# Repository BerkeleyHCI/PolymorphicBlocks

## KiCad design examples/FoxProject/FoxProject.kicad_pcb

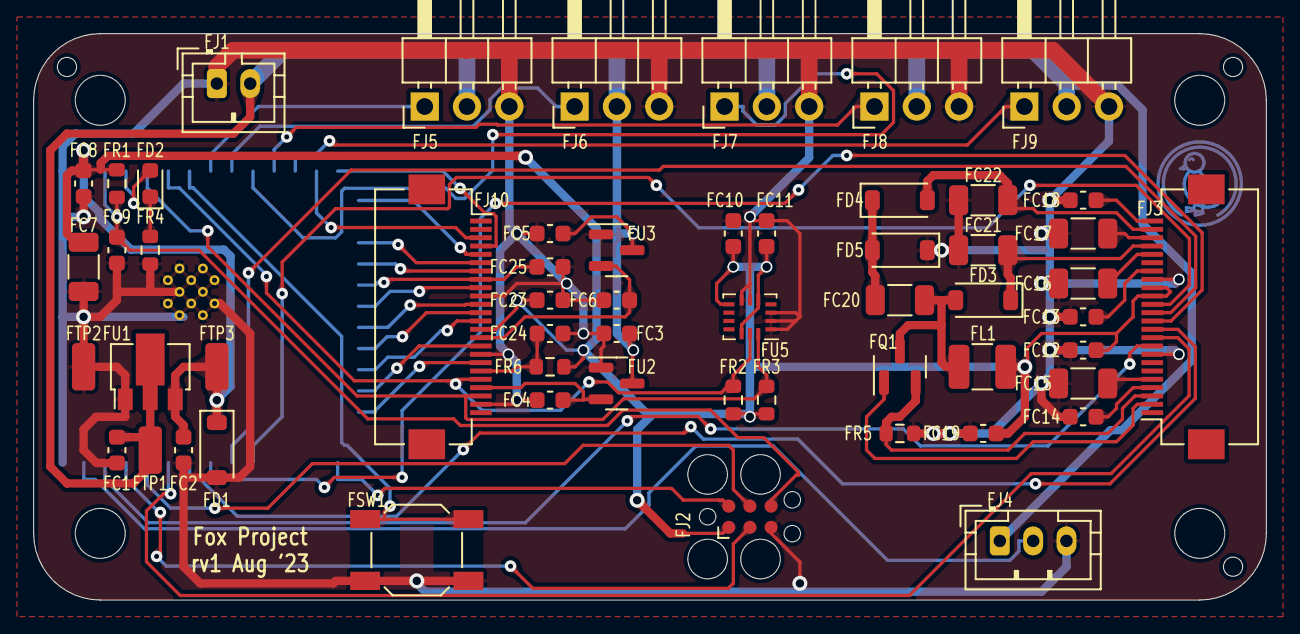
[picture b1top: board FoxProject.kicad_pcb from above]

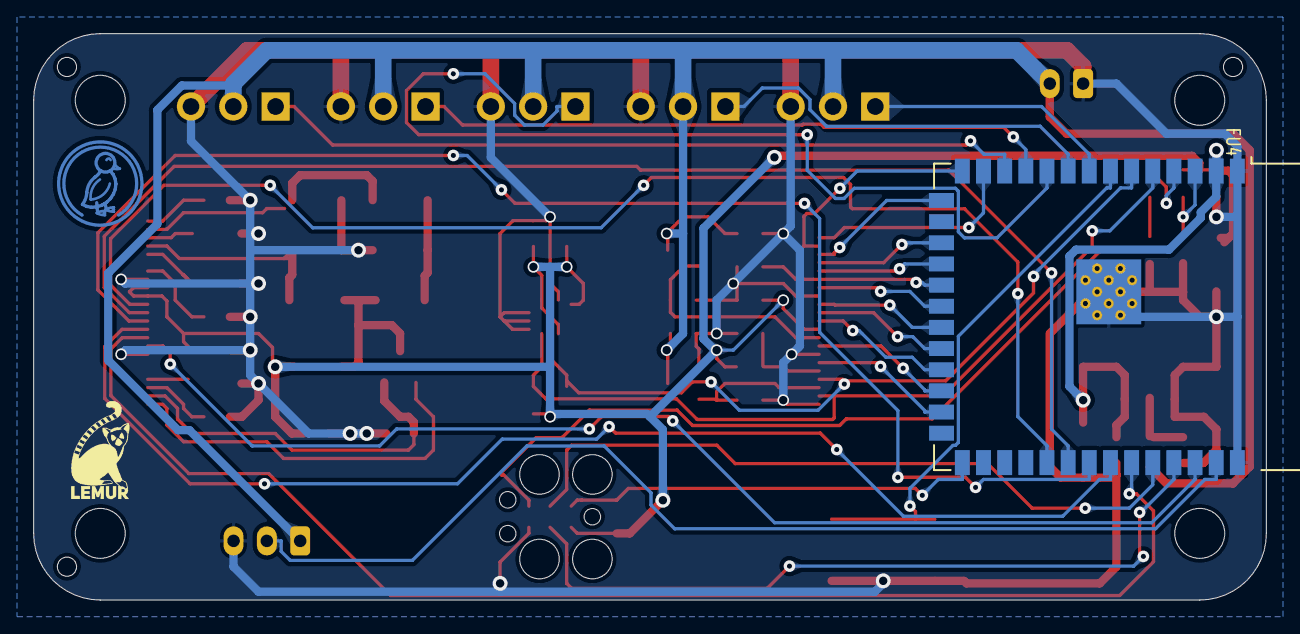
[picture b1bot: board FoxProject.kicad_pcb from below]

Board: 2 copper layers, 74.0 x 34.0 mm, 66 parts (3 on the bottom side), 51 nets.

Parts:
FC1, FC2, FC3, FC4, FC5, FC6, FC8, FC9, FC10, FC11, FC12, FC13, FC14, FC18, FC19, FC23, FC24, FC25: C_0603_1608Metric
FC7, FC15, FC16, FC17, FC20, FC21, FC22: C_1206_3216Metric
FD1: BZT52C3V6 (SMC(Sangdest Microelectronicstronic (N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; D_SOD-123
FD2: LED_0603_1608Metric
FD3, FD4, FD5: B5817W (Guangdong Hottech) - 20V 450mV@1A 300mA S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; D_SOD-123
FH1, FH2, FH3: JlcToolingHole_1.152mm
FJ1: B2B-PH-K (JST); JST_PH_B2B-PH-K_1x02_P2.00mm_Vertical
FJ2: Tag-Connect_TC2030-IDC-FP_2x03_P1.27mm_Vertical
FJ3, FJ10: AFC01-S24FCA-00 (Jushuo); Hirose_FH12-24S-0.5SH_1x24-1MP_P0.50mm_Horizontal
FJ4: B3B-PH-K (JST); JST_PH_B3B-PH-K_1x03_P2.00mm_Vertical
FJ5, FJ6, FJ7, FJ8, FJ9: PinHeader2.54 1x3 Horizontal (Generic); PinHeader_1x03_P2.54mm_Horizontal
FL1: L_1210_3225Metric
FQ1: AO3400A (Alpha & Omega Semicon) - 30V 5.7A 26.5m?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; SOT-23
FR1, FR2, FR3, FR4, FR5, FR6: R_0603_1608Metric
FSW1: 5.1mm switch; SW_SPST_SKQG_WithoutStem
FTP1: 5015 (Keystone) - pwr; TestPoint_TE_RCT_0805
FTP2: 5015 (Keystone) - gnd; TestPoint_TE_RCT_0805
FTP3: 5015 (Keystone) - v3v3; TestPoint_TE_RCT_0805
FU1: AP7215-33YG-13 (Diodes Incorporated); SOT-89-3
FU2: XC6206P252MR (Torex Semiconductor Ltd); SOT-23
FU3: XC6206P122MR-G (Torex Semiconductor Ltd); SOT-23
FU4: ESP32-S3-WROOM-1-N16R8 (Espressif Systems); ESP32-S3-WROOM-1
FU5: LSM6DS3TR-C (STMicroelectronics); Bosch_LGA-14_3x2.5mm_P0.5mm
H10, H11, H12, H13: MountingHole_3mm
UU4: Duck; Symbol_Duckling
UU5: Lemur; Symbol_LemurSmall

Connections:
Fcam.device.reset: FC24.1, FJ10.19, FR6.2
Fcam.dvp8.href: FJ10.16, FU4.24
Fcam.dvp8.pclk: FC25.1, FJ10.8, FU4.19
Fcam.dvp8.vsync: FJ10.18, FU4.25
Fcam.dvp8.xclk: FJ10.12, FU4.22
Fcam.dvp8.y0: FJ10.6, FU4.17
Fcam.dvp8.y1: FJ10.4, FU4.14
Fcam.dvp8.y2: FJ10.3, FU4.13
Fcam.dvp8.y3: FJ10.5, FU4.15
Fcam.dvp8.y4: FJ10.7, FU4.18
Fcam.dvp8.y5: FJ10.9, FU4.20
Fcam.dvp8.y6: FJ10.11, FU4.21
Fcam.dvp8.y7: FJ10.13, FU4.23
Fepd.boost.boot_cap.neg: FC20.2, FD4.1, FD5.2
Fepd.boost.inductor.b: FC20.1, FD3.2, FL1.2, FQ1.3
Fepd.boost.neg_out: FC22.2, FD4.2, FJ3.23
Fepd.boost.pos_out: FC21.1, FD3.1, FJ3.21
Fepd.busy: FJ3.9, FU4.38
Fepd.cs: FJ3.12, FU4.33
Fepd.dc: FJ3.11, FU4.34
Fepd.device.gdr: FJ3.2, FQ1.1
Fepd.device.rese: FJ3.3, FQ1.2, FR5.1
Fepd.device.vcom: FC18.1, FJ3.24
Fepd.device.vdd1v8: FC13.1, FJ3.18
Fepd.device.vgh: FC15.1, FJ3.5
Fepd.device.vgl: FC14.2, FJ3.4
Fepd.device.vsh: FC16.1, FJ3.20
Fepd.device.vsl: FC17.2, FJ3.22
Fepd.reset: FJ3.10, FU4.35
Fepd.spi.mosi: FJ3.14, FU4.31
Fepd.spi.sck: FJ3.13, FU4.32
Fgnd: FC1.2, FC2.2, FC3.2, FC4.2, FC5.2, FC6.2, FC7.2, FC8.2, FC9.2, FC10.2, FC11.2, FC12.2, FC13.2, FC14.1, FC15.2, FC16.2, FC17.1, FC18.2, FC19.2, FC21.2, FC22.1, FC23.2, FC24.2, FC25.2, FD1.2, FD5.1, FJ1.1, FJ2.5, FJ3.8, FJ3.17, FJ4.3, FJ5.3, FJ6.3, FJ7.3, FJ8.3, FJ9.3, FJ10.10, FJ10.17, FJ10.23, FR4.2, FR5.2, FSW1.2, FTP2.1, FU1.1, FU2.1, FU3.1, FU4.1, FU4.40, FU4.41, FU5.1, FU5.2, FU5.3, FU5.6, FU5.7
Fi2c_chain_0.scl: FJ10.20, FR2.2, FU4.6, FU5.13
Fi2c_chain_0.sda: FJ10.22, FR3.2, FU4.5, FU5.14
Fled.res.a: FD2.1, FR4.1
Fled.signal: FD2.2, FU4.4
Fmcu.program_boot_node: FJ2.2, FU4.27
Fmcu.program_en_node: FC9.1, FJ2.6, FR1.2, FU4.3
Fmcu.program_uart_node.a_tx: FJ2.3, FU4.37
Fmcu.program_uart_node.b_tx: FJ2.4, FU4.36
Fpixels.din: FJ4.2, FU4.39
Fpwr: FC1.1, FC3.1, FC5.1, FJ1.2, FJ4.1, FJ5.2, FJ6.2, FJ7.2, FJ8.2, FJ9.2, FTP1.1, FU1.2, FU2.3, FU3.3
Fservos[0].pwm: FJ5.1, FU4.8
Fservos[1].pwm: FJ6.1, FU4.9
Fservos[2].pwm: FJ7.1, FU4.10
Fservos[3].pwm: FJ8.1, FU4.11
Fservos[4].pwm: FJ9.1, FU4.12
Fsw.out: FSW1.1, FU4.7
Fv1v2: FC6.1, FJ10.15, FU3.2
Fv2v5: FC4.1, FJ10.21, FU2.2
Fv3v3: FC2.1, FC7.1, FC8.1, FC10.1, FC11.1, FC12.1, FC19.1, FC23.1, FD1.1, FJ2.1, FJ3.15, FJ3.16, FJ10.14, FL1.1, FR1.1, FR2.1, FR3.1, FR6.1, FTP3.1, FU1.3, FU4.2, FU5.5, FU5.8, FU5.12

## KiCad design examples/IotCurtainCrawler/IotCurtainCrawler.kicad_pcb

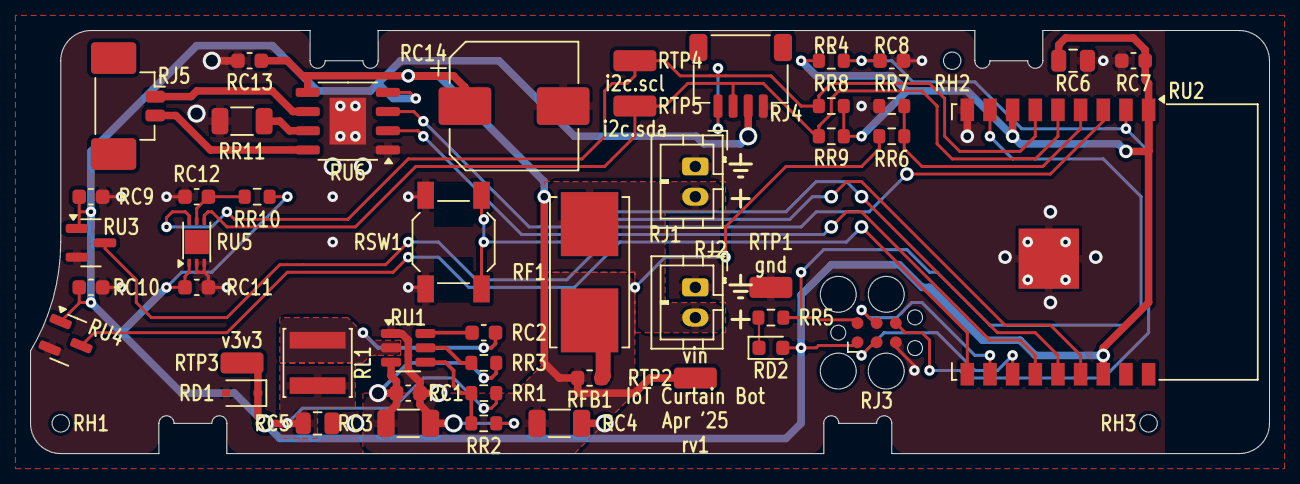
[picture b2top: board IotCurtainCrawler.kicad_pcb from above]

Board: 2 copper layers, 82.0 x 28.0 mm, 50 parts (0 on the bottom side), 26 nets.

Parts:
RC1: reg_3v3.hf_in_cap; C_0603_1608Metric
RC2: reg_3v3.boot_cap; C_0603_1608Metric
RC3: reg_3v3.power_path.in_cap.c[0]; C_1206_3216Metric
RC4: reg_3v3.power_path.in_cap.c[1]; C_1206_3216Metric
RC5: reg_3v3.power_path.out_cap; C_0805_2012Metric
RC6: mcu.vcc_cap0; C_0805_2012Metric
RC7: mcu.vcc_cap1; C_0603_1608Metric
RC8: mcu.en_pull.c; C_0603_1608Metric
RC9: enca.cin; C_0603_1608Metric
RC10: encb.cin; C_0603_1608Metric
RC11: als.vcc_cap; C_0603_1608Metric
RC12: als.dvi_cap; C_0603_1608Metric
RC13: drv.vm_cap0; C_0603_1608Metric
RC14: drv.vm_cap1; CP_Elec_8x10
RD1: prot_3v3; D_SOD-323
RD2: ledr.package; LED_0603_1608Metric
RF1: fuse; Fuseholder_Littelfuse_Nano2_154x
RFB1: ferrite; L_0603_1608Metric
RH1: jlc_th.th1; JlcToolingHole_1.152mm
RH2: jlc_th.th2; JlcToolingHole_1.152mm
RH3: jlc_th.th3; JlcToolingHole_1.152mm
RJ1: pwr; JST_PH_B2B-PH-K_1x02_P2.00mm_Vertical
RJ2: pwr_out; JST_PH_B2B-PH-K_1x02_P2.00mm_Vertical
RJ3: mcu.prog; Tag-Connect_TC2030-IDC-FP_2x03_P1.27mm_Vertical
RJ4: qwiic; JST_SH_SM04B-SRSS-TB_1x04-1MP_P1.00mm_Horizontal
RJ5: motor; Molex_PicoBlade_53398-0271_1x02-1MP_P1.25mm_Vertical
RL1: reg_3v3.power_path.inductor; L_Sunlord_SWPA4030S
RR1: reg_3v3.fb.top_res; R_0603_1608Metric
RR2: reg_3v3.fb.bottom_res; R_0603_1608Metric
RR3: reg_3v3.en_res; R_0603_1608Metric
RR4: mcu.en_pull.r; R_0603_1608Metric
RR5: ledr.res; R_0603_1608Metric
RR6: vin_sense.top_res; R_0603_1608Metric
RR7: vin_sense.bottom_res; R_0603_1608Metric
RR8: i2c_pull.scl_res; R_0603_1608Metric
RR9: i2c_pull.sda_res; R_0603_1608Metric
RR10: als.dvi_res; R_0603_1608Metric
RR11: drv.isen_res; R_1206_3216Metric
RSW1: sw; SW_SPST_SKQG_WithoutStem
RTP1: gnd; TestPoint_TE_RCT_0805
RTP2: vin; TestPoint_TE_RCT_0805
RTP3: v3v3; TestPoint_TE_RCT_0805
RTP4: i2c.scl; TestPoint_TE_RCT_0805
RTP5: i2c.sda; TestPoint_TE_RCT_0805
RU1: reg_3v3.ic; SOT-23-6
RU2: mcu.ic; ESP-WROOM-02
RU3: enca.ic; SOT-23
RU4: encb.ic; SOT-23
RU5: als.ic; HVSOF6
RU6: drv.ic; HSOP-8-1EP_3.9x4.9mm_P1.27mm_EP2.41x3.1mm

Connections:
Rals.dvi_res.b: RC12.1, RR10.2, RU5.5
Rdrv.ic.isen: RR11.2, RU6.7
Rdrv.in1: RU2.14, RU6.3
Rdrv.in2: RU2.15, RU6.2
Rdrv.out1: RJ5.1, RU6.6
Rdrv.out2: RJ5.2, RU6.8
Renca.out: RU2.13, RU3.3
Rencb.out: RU2.10, RU4.3
Rfuse.pwr_out: RF1.2, RFB1.1
Rgnd: RC1.2, RC3.2, RC4.2, RC5.2, RC6.2, RC7.2, RC8.2, RC9.2, RC10.2, RC11.2, RC12.2, RC13.2, RC14.2, RD1.2, RJ1.1, RJ2.1, RJ3.5, RJ4.1, RR2.2, RR7.2, RR11.1, RSW1.2, RTP1.1, RU1.1, RU2.9, RU2.19, RU3.2, RU4.2, RU5.2, RU5.3, RU6.1, RU6.9
Ri2c_chain_0.scl: RJ4.4, RR8.2, RTP4.1, RU2.6, RU5.6
Ri2c_chain_0.sda: RJ4.3, RR9.2, RTP5.1, RU2.5, RU5.4
Rledr.res.a: RD2.1, RR5.1
Rmcu.program_boot_node: RJ3.2, RR5.2, RU2.8
Rmcu.program_en_node: RC8.1, RJ3.6, RR4.2, RU2.2
Rmcu.program_uart_node.a_tx: RJ3.3, RU2.12
Rmcu.program_uart_node.b_tx: RJ3.4, RU2.11
Rreg_3v3.boot_cap.neg: RC2.2, RL1.1, RU1.2
Rreg_3v3.boot_cap.pos: RC2.1, RU1.6
Rreg_3v3.en_res.b: RR3.2, RU1.5
Rreg_3v3.fb.output: RR1.2, RR2.1, RU1.4
Rsw.out: RSW1.1, RU2.3
Rv3v3: RC5.1, RC6.1, RC7.1, RC9.1, RC10.1, RC11.1, RD1.1, RD2.2, RJ3.1, RJ4.2, RL1.2, RR1.1, RR4.1, RR8.1, RR9.1, RR10.1, RTP3.1, RU2.1, RU2.7, RU2.16, RU3.1, RU4.1, RU5.1, RU6.4
Rvin: RC1.1, RC3.1, RC4.1, RC13.1, RC14.1, RFB1.2, RR3.1, RR6.1, RTP2.1, RU1.3, RU6.5
Rvin_raw: RF1.1, RJ1.2, RJ2.2
Rvin_sense.output: RR6.2, RR7.1, RU2.4

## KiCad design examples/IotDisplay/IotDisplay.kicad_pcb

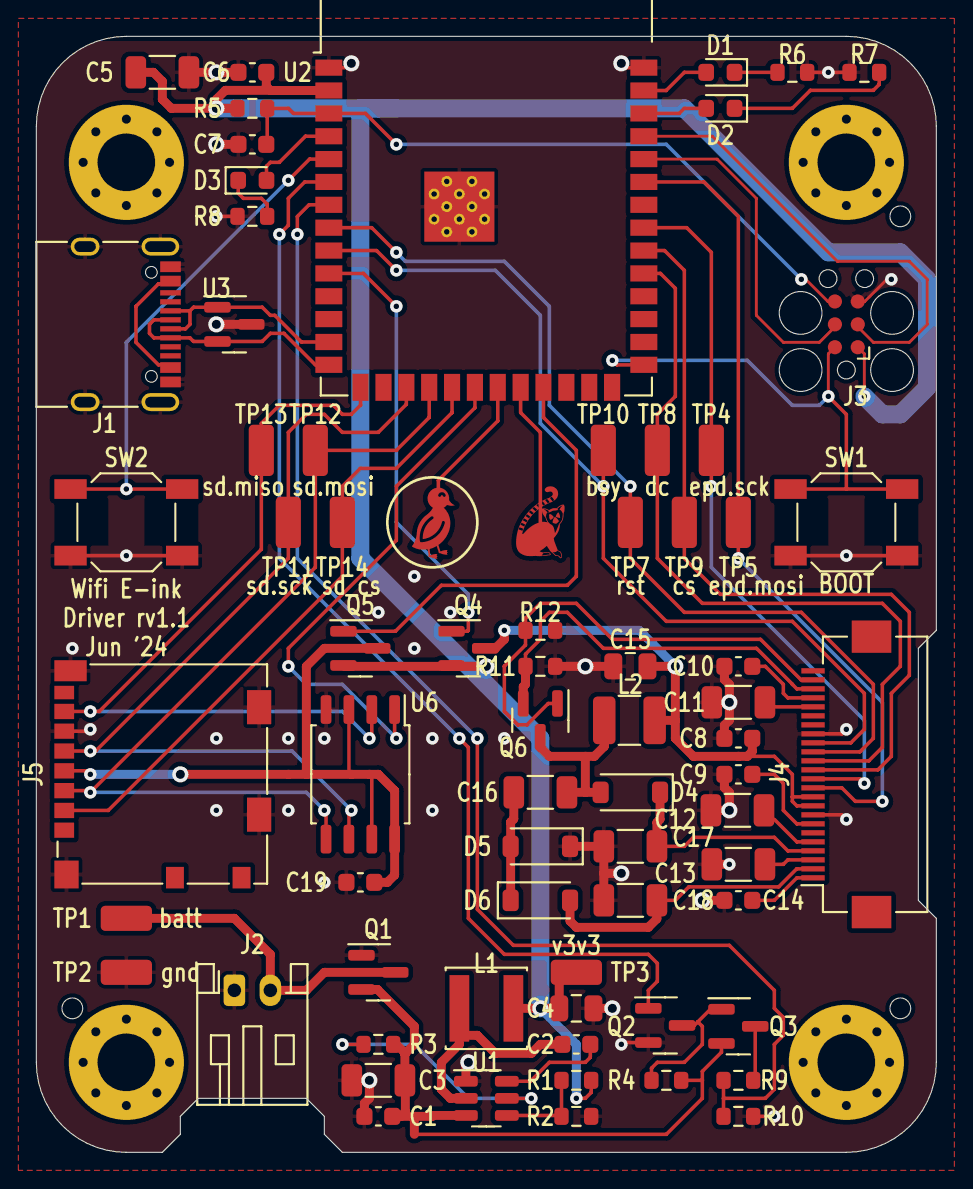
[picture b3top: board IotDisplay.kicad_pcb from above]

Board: 2 copper layers, 50.0 x 62.0 mm, 74 parts (0 on the bottom side), 55 nets.

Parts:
C1, C2, C6, C7, C8, C9, C10, C14, C19: C_0603_1608Metric
C3, C5, C11, C12, C13, C16, C17, C18: C_1206_3216Metric
C4, C15: C_0805_2012Metric
D1: Red 615~630nm 1.9~2.2V 0603 Light Emitting Diodes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; LED_0603_1608Metric
D2, D3: LED_0603_1608Metric
D4, D5, D6: 20V 450mV@1A 300mA SOD-123 Schottky Barrier Diode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; D_SOD-123
H1, H2, H3: JlcToolingHole_1.152mm
J1: COM-15111; USB_C_Receptacle_XKB_U262-16XN-4BVC11
J2: S2B-PH-K; JST_PH_S2B-PH-K_1x02_P2.00mm_Horizontal
J3: Tag-Connect_TC2030-IDC-FP_2x03_P1.27mm_Vertical
J4: AFC07-S24ECA-00; Hirose_FH12-24S-0.5SH_1x24-1MP_P0.50mm_Horizontal
J5: 104031-0811; microSD_HC_Molex_104031-0811
L1: L_Sunlord_SWPA4030S
L2: L_1210_3225Metric
Q1, Q3, Q4, Q5: 30V 4A 44m?@10V,4.3A 1.4W 1.3V@250?A P Channel SO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; SOT-23
Q2: 60V 115mA 200mW 7.5?@10V,500mA 2.5V@250?A N Chann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; SOT-23
Q6: 30V 5.7A 26.5m?@10V,5.7A 1.4W 1.5V@250?A N Channe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; SOT-23
R1, R2, R3, R4, R5, R6, R7, R8, R9, R10, R11, R12: R_0603_1608Metric
SW1, SW2: 5.1mm switch; SW_SPST_SKQG_WithoutStem
TP1: batt; TestPoint_TE_RCT_0805
TP2: gnd; TestPoint_TE_RCT_0805
TP3: v3v3; TestPoint_TE_RCT_0805
TP4: epd.sck; TestPoint_TE_RCT_0805
TP5: epd.mosi; TestPoint_TE_RCT_0805
TP7: rst; TestPoint_TE_RCT_0805
TP8: dc; TestPoint_TE_RCT_0805
TP9: cs; TestPoint_TE_RCT_0805
TP10: bsy; TestPoint_TE_RCT_0805
TP11: sd.sck; TestPoint_TE_RCT_0805
TP12: sd.mosi; TestPoint_TE_RCT_0805
TP13: sd.miso; TestPoint_TE_RCT_0805
TP14: sd_cs; TestPoint_TE_RCT_0805
U1: TPS54202H; SOT-23-6
U2: ESP32-S3-WROOM-1-N16R8; ESP32-S3-WROOM-1
U3: PESD5V0X1BT; SOT-23
U4: Symbol_DucklingSolid
U5: Symbol_LemurSolid
U6: W25Q128JVSIQ; SOIC-8_5.23x5.23mm_P1.27mm

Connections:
batt.pwr: J2.2, Q1.3, TP1.1
epd.boost.boot_cap.neg: C16.2, D5.1, D6.2
epd.boost.inductor.b: C16.1, D4.2, L2.2, Q6.3
epd.boost.neg_out: C18.2, D5.2, J4.2
epd.boost.pos_out: C17.1, D4.1, J4.4
epd.device.gdr: J4.23, Q6.1, R12.1
epd.device.rese: J4.22, Q6.2, R11.1
epd.device.vcom: C14.1, J4.1
epd.device.vdd1v8: C9.1, J4.7
epd.device.vgh: C11.1, J4.20
epd.device.vgl: C10.2, J4.21
epd.device.vsh: C12.1, J4.5
epd.device.vsl: C13.2, J4.3
epd_gate.control: Q4.1, U2.10
epd_gate.output: C8.1, C15.1, J4.9, J4.10, L2.1, Q4.3
flash.cs: U2.20, U6.1
gnd: C1.2, C3.2, C4.2, C5.2, C6.2, C7.2, C8.2, C9.2, C10.1, C11.2, C12.2, C13.1, C14.2, C15.2, C17.2, C18.1, C19.2, D6.1, J1.A1, J1.A12, J1.B1, J1.B12, J1.S1, J2.1, J3.5, J4.8, J4.17, J5.6, J5.11, Q1.1, Q2.2, R2.2, R6.2, R7.2, R8.2, R10.2, R11.2, R12.2, SW1.2, SW2.2, TP2.1, U1.1, U2.1, U2.40, U2.41, U3.3, U6.4
ledb.res.a: D3.1, R8.1
ledb.signal: D3.2, U2.4
ledg.res.a: D2.1, R7.1
ledg.signal: D2.2, U2.38
ledr.res.a: D1.1, R6.1
ledr.signal: D1.2, U2.39
mcu.program_boot_node: J3.2, SW1.1, U2.27
mcu.program_en_node: C7.1, J3.6, R5.2, U2.3
mcu.program_uart_node.a_tx: J3.3, U2.37
mcu.program_uart_node.b_tx: J3.4, U2.36
mem_gate.control: Q5.1, U2.23
mem_gate.output: C19.1, J5.4, Q5.3, U6.3, U6.7, U6.8
reg_3v3.boot_cap.neg: C2.2, L1.1, U1.2
reg_3v3.boot_cap.pos: C2.1, U1.6
reg_3v3.en_res.b: R3.2, U1.5
reg_3v3.fb.output: R1.2, R2.1, U1.4
sw.out: SW2.1, U2.5
touch_duck.pad: U2.21, U4.1
touch_lemur.pad: U2.22, U5.1
tp_busy.io: J4.16, TP10.1, U2.9
tp_dc.io: J4.14, TP8.1, U2.31
tp_epd.io.mosi: J4.11, TP5.1, U2.35
tp_epd.io.sck: J4.12, TP4.1, U2.33
tp_epd_cs.io: J4.13, TP9.1, U2.32
tp_erst.io: J4.15, TP7.1, U2.8
tp_sd.io.miso: J5.7, TP13.1, U2.15, U6.2
tp_sd.io.mosi: J5.3, TP12.1, U2.18, U6.5
tp_sd.io.sck: J5.5, TP11.1, U2.17, U6.6
tp_sd_cs.io: J5.2, TP14.1, U2.19
usb.pwr: J1.A4, J1.A9, J1.B4, J1.B9
usb_chain_0.d_N: J1.A7, J1.B7, U2.13, U3.1
usb_chain_0.d_P: J1.A6, J1.B6, U2.14, U3.2
v3v3: C4.1, C5.1, C6.1, J3.1, L1.2, Q4.2, Q5.2, R1.1, R5.1, TP3.1, U2.2
vbat: C1.1, C3.1, Q1.2, Q3.2, R3.1, R4.1, U1.3
vbat_sense.output: R9.2, R10.1, U2.7
vbat_sense_gate.control: Q2.1, U2.6
vbat_sense_gate.output: Q3.3, R9.1
vbat_sense_gate.pre.drain: Q2.3, Q3.1, R4.2

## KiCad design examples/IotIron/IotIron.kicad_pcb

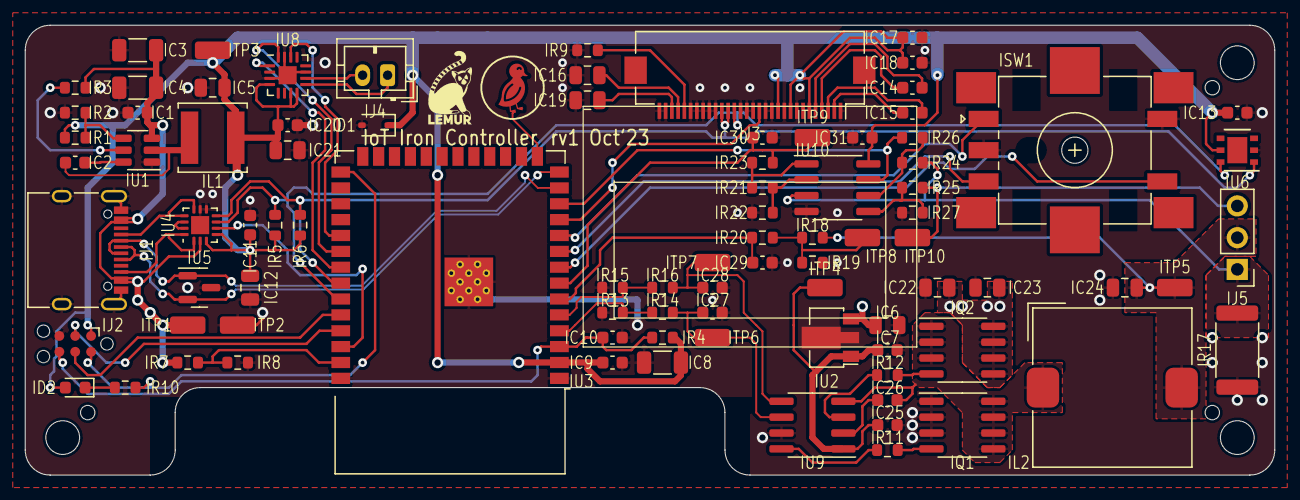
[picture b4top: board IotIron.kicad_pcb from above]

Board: 2 copper layers, 100.0 x 36.0 mm, 98 parts (0 on the bottom side), 59 nets.

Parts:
H10, H11, H14: MountingHole_2.7mm_M2.5
IC1, IC2, IC7, IC9, IC10, IC11, IC13, IC14, IC15, IC17, IC18, IC20, IC25, IC26, IC27, IC28, IC29, IC30, IC31: C_0603_1608Metric
IC3, IC4, IC8: C_1206_3216Metric
IC5, IC6, IC12, IC16, IC19, IC21, IC22, IC23, IC24: C_0805_2012Metric
ID1: BZT52B3V6S (SMC(Sangdest Microelectronicstronic (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; D_SOD-323
ID2: KT-0603R (Hubei KENTO Elec) - Red 615~630nm 1.9~2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; LED_0603_1608Metric
IH1, IH2, IH3: JlcToolingHole_1.152mm
IJ1: COM-15111 (Sparkfun); USB_C_Receptacle_XKB_U262-16XN-4BVC11
IJ2: Tag-Connect_TC2030-IDC-NL_2x03_P1.27mm_Vertical
IJ3: AFC01-S30FCA-00 (Jushuo); Hirose_FH12-30S-0.5SH_1x30-1MP_P0.50mm_Horizontal
IJ4: B2B-PH-K (JST); JST_PH_B2B-PH-K_1x02_P2.00mm_Vertical
IJ5: PinHeader2.54 1x3 (Generic); PinHeader_1x03_P2.54mm_Vertical
IL1: L_Sunlord_SWPA5040S
IL2: L_TDK_SLF12565
IQ1, IQ2: IRF7458TRPBF (Infineon Technologies) - 30V 14A 8m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; SOIC-8_3.9x4.9mm_P1.27mm
IR1, IR2, IR3, IR4, IR5, IR6, IR7, IR8, IR9, IR10, IR11, IR12, IR13, IR14, IR15, IR16, IR18, IR19, IR20, IR21, IR22, IR23, IR24, IR25, IR26, IR27: R_0603_1608Metric
IR17: R_2512_6332Metric
ISW1: EC11J1525402 (Alps Alpine); RotaryEncoder_Alps_EC11J15-Switch
ITP1: 5015 (Keystone) - vusb; TestPoint_TE_RCT_0805
ITP2: 5015 (Keystone) - gnd; TestPoint_TE_RCT_0805
ITP3: 5015 (Keystone) - v3v3; TestPoint_TE_RCT_0805
ITP4: 5015 (Keystone) - vgate; TestPoint_TE_RCT_0805
ITP5: 5015 (Keystone) - conv_out; TestPoint_TE_RCT_0805
ITP6: 5015 (Keystone) - _low_rc_output_link; TestPoint_TE_RCT_0805
ITP7: 5015 (Keystone) - _high_rc_output_link; TestPoint_TE_RCT_0805
ITP8: 5015 (Keystone) - _vsense_output_link; TestPoint_TE_RCT_0805
ITP9: 5015 (Keystone) - _tp_i_output_link; TestPoint_TE_RCT_0805
ITP10: 5015 (Keystone) - _tamp_input_positive_link; TestPoint_TE_RCT_0805
IU1: TPS54202H (Texas Instruments); SOT-23-6
IU2: L78L12AC (STMicroelectronics); SOT-89-3
IU3: ESP32-S3-WROOM-1-N16R8 (Espressif Systems); ESP32-S3-WROOM-1
IU4: FUSB302B11MPX (ON Semiconductor); WQFN-14-1EP_2.5x2.5mm_P0.5mm_EP1.45x1.45mm
IU5: PESD5V0X1BT (Nexperia); SOT-23
IU6: HDC1080 (Texas Instruments); WSON-6-1EP_3x3mm_P0.95mm
IU7: ER-OLED-0.96-1.1 (EastRising); Lcd_Er_Oled0.96_1.1_Outline
IU8: MAX98357AETE+T (Maxim Integrated); QFN-16-1EP_3x3mm_P0.5mm_EP1.45x1.45mm
IU9: UCC27282DR (Texas Instruments); SOIC-8_3.9x4.9mm_P1.27mm
IU10: OPA2333AIDR (Texas Instruments); SOIC-8_3.9x4.9mm_P1.27mm
UU5: Lemur; Symbol_LemurSmall
svg2mod: G***; Symbol_DucklingSolid

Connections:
Iconv.sw.driver.ic.hb: IC26.1, IU9.2
Iconv.sw.high_gate_res.a: IR12.1, IU9.3
Iconv.sw.high_gate_res.b: IQ2.4, IR12.2
Iconv.sw.low_gate_res.a: IR11.1, IU9.8
Iconv.sw.low_gate_res.b: IQ1.4, IR11.2
Iconv.sw.out: IC26.2, IL2.1, IQ1.5, IQ1.6, IQ1.7, IQ1.8, IQ2.1, IQ2.2, IQ2.3, IU9.4
Iconv_out: IC24.1, IJ5.2, IL2.2, IR18.1, ITP5.1
Ienc.a: ISW1.A, IU3.10
Ienc.b: ISW1.B, IU3.9
Ienc.sw: ISW1.S1, IU3.8
Ignd: IC1.2, IC3.2, IC4.2, IC5.2, IC6.2, IC7.2, IC8.2, IC9.2, IC10.2, IC11.2, IC12.2, IC13.2, IC16.2, IC17.2, IC18.2, IC19.2, IC20.2, IC21.2, IC22.2, IC23.2, IC24.2, IC25.2, IC27.2, IC28.2, IC29.2, IC30.2, IC31.2, ID1.2, IJ1.A1, IJ1.A12, IJ1.B1, IJ1.B12, IJ1.S1, IJ2.5, IJ3.1, IJ3.8, IJ3.10, IJ3.12, IJ3.13, IJ3.15, IJ3.16, IJ3.17, IJ3.21, IJ3.22, IJ3.23, IJ3.24, IJ3.25, IJ3.29, IJ3.30, IQ1.1, IQ1.2, IQ1.3, IR2.2, IR8.2, IR9.2, IR13.1, IR15.1, IR17.1, IR19.2, IR22.2, IR27.1, ISW1.C, ISW1.S2, ITP2.1, IU1.1, IU2.2, IU3.1, IU3.40, IU3.41, IU4.8, IU4.9, IU4.15, IU5.3, IU6.2, IU8.3, IU8.11, IU8.15, IU8.17, IU9.7, IU10.4
Ihigh_pull.io: IR15.2, IR16.1, IU3.5
Ihigh_rc.output: IC28.1, IR16.2, ITP7.1, IU9.5
Ii2c_pull.i2c.scl: IJ3.18, IR5.2, IU3.35, IU4.6, IU6.6
Ii2c_pull.i2c.sda: IJ3.19, IJ3.20, IR6.2, IU3.34, IU4.7, IU6.1
Iifilt.output: IR21.1, IR23.1, IU10.1
Iisense.pwr_out: IJ5.1, IR17.2, IR24.1, IU10.3
Iledr.res.a: ID2.1, IR10.1
Ilow_pull.io: IR13.2, IR14.1, IU3.4
Ilow_rc.output: IC27.1, IR14.2, ITP6.1, IU9.6
Imcu.program_boot_node: IJ2.2, IR10.2, IU3.27
Imcu.program_en_node: IC10.1, IJ2.6, IR4.2, IU3.3
Imcu.program_uart_node.a_tx: IJ2.3, IU3.37
Imcu.program_uart_node.b_tx: IJ2.4, IU3.36
Ioled.c1_cap.neg: IC14.2, IJ3.5
Ioled.c1_cap.pos: IC14.1, IJ3.4
Ioled.c2_cap.neg: IC15.2, IJ3.3
Ioled.c2_cap.pos: IC15.1, IJ3.2
Ioled.device.vcc: IC19.1, IJ3.28
Ioled.device.vcomh: IC16.1, IJ3.27
Ioled.iref_res.a: IJ3.26, IR9.1
Ioled.reset: IJ3.14, IU3.11
Ipacked_opamp.inn.0: IR21.2, IR22.1, IU10.2
Ipacked_opamp.inn.1: IR24.2, IR26.2, IU10.6
Ipacked_opamp.inp.1: IR25.2, IR27.2, IU10.5
Ipd.ic.vconn: IU4.12, IU4.13
Ipd.int: IU3.38, IU4.5
Ireg_3v3.boot_cap.neg: IC2.2, IL1.1, IU1.2
Ireg_3v3.boot_cap.pos: IC2.1, IU1.6
Ireg_3v3.en_res.b: IR3.2, IU1.5
Ireg_3v3.fb.output: IR1.2, IR2.1, IU1.4
Ispk_drv.i2s.sck: IU3.32, IU8.16
Ispk_drv.i2s.sd: IU3.33, IU8.1
Ispk_drv.i2s.ws: IU3.31, IU8.14
Ispk_drv.out.a: IJ4.1, IU8.9
Ispk_drv.out.b: IJ4.2, IU8.10
Itamp.input_positive: IJ5.3, IR25.1, ITP10.1
Itamp.output: IR26.1, IU3.12, IU10.7
Itp_i.output: IC30.1, IR23.2, ITP9.1, IU3.7
Iusb.A5: IJ1.A5, IU4.10, IU4.11
Iusb.B5: IJ1.B5, IU4.1, IU4.14
Iusb_chain_0.d_N: IJ1.A7, IJ1.B7, IU3.13, IU5.1
Iusb_chain_0.d_P: IJ1.A6, IJ1.B6, IU3.14, IU5.2
Iv3v3: IC5.1, IC8.1, IC9.1, IC11.1, IC12.1, IC13.1, IC17.1, IC18.1, IC20.1, IC21.1, IC31.1, ID1.1, ID2.2, IJ2.1, IJ3.6, IJ3.9, IJ3.11, IL1.2, IR1.1, IR4.1, IR5.1, IR6.1, ITP3.1, IU3.2, IU4.3, IU4.4, IU6.5, IU8.4, IU8.7, IU8.8, IU10.8
Ivfilt.output: IC29.1, IR20.2, IU3.6
Ivgate: IC7.1, IC25.1, ITP4.1, IU2.1, IU9.1
Ivsense.output: IR18.2, IR19.1, IR20.1, ITP8.1
Ivusb: IC1.1, IC3.1, IC4.1, IC6.1, IC22.1, IC23.1, IJ1.A4, IJ1.A9, IJ1.B4, IJ1.B9, IQ2.5, IQ2.6, IQ2.7, IQ2.8, IR3.1, IR7.1, ITP1.1, IU1.3, IU2.3, IU4.2
Ivusb_sense.output: IR7.2, IR8.1, IU3.39
